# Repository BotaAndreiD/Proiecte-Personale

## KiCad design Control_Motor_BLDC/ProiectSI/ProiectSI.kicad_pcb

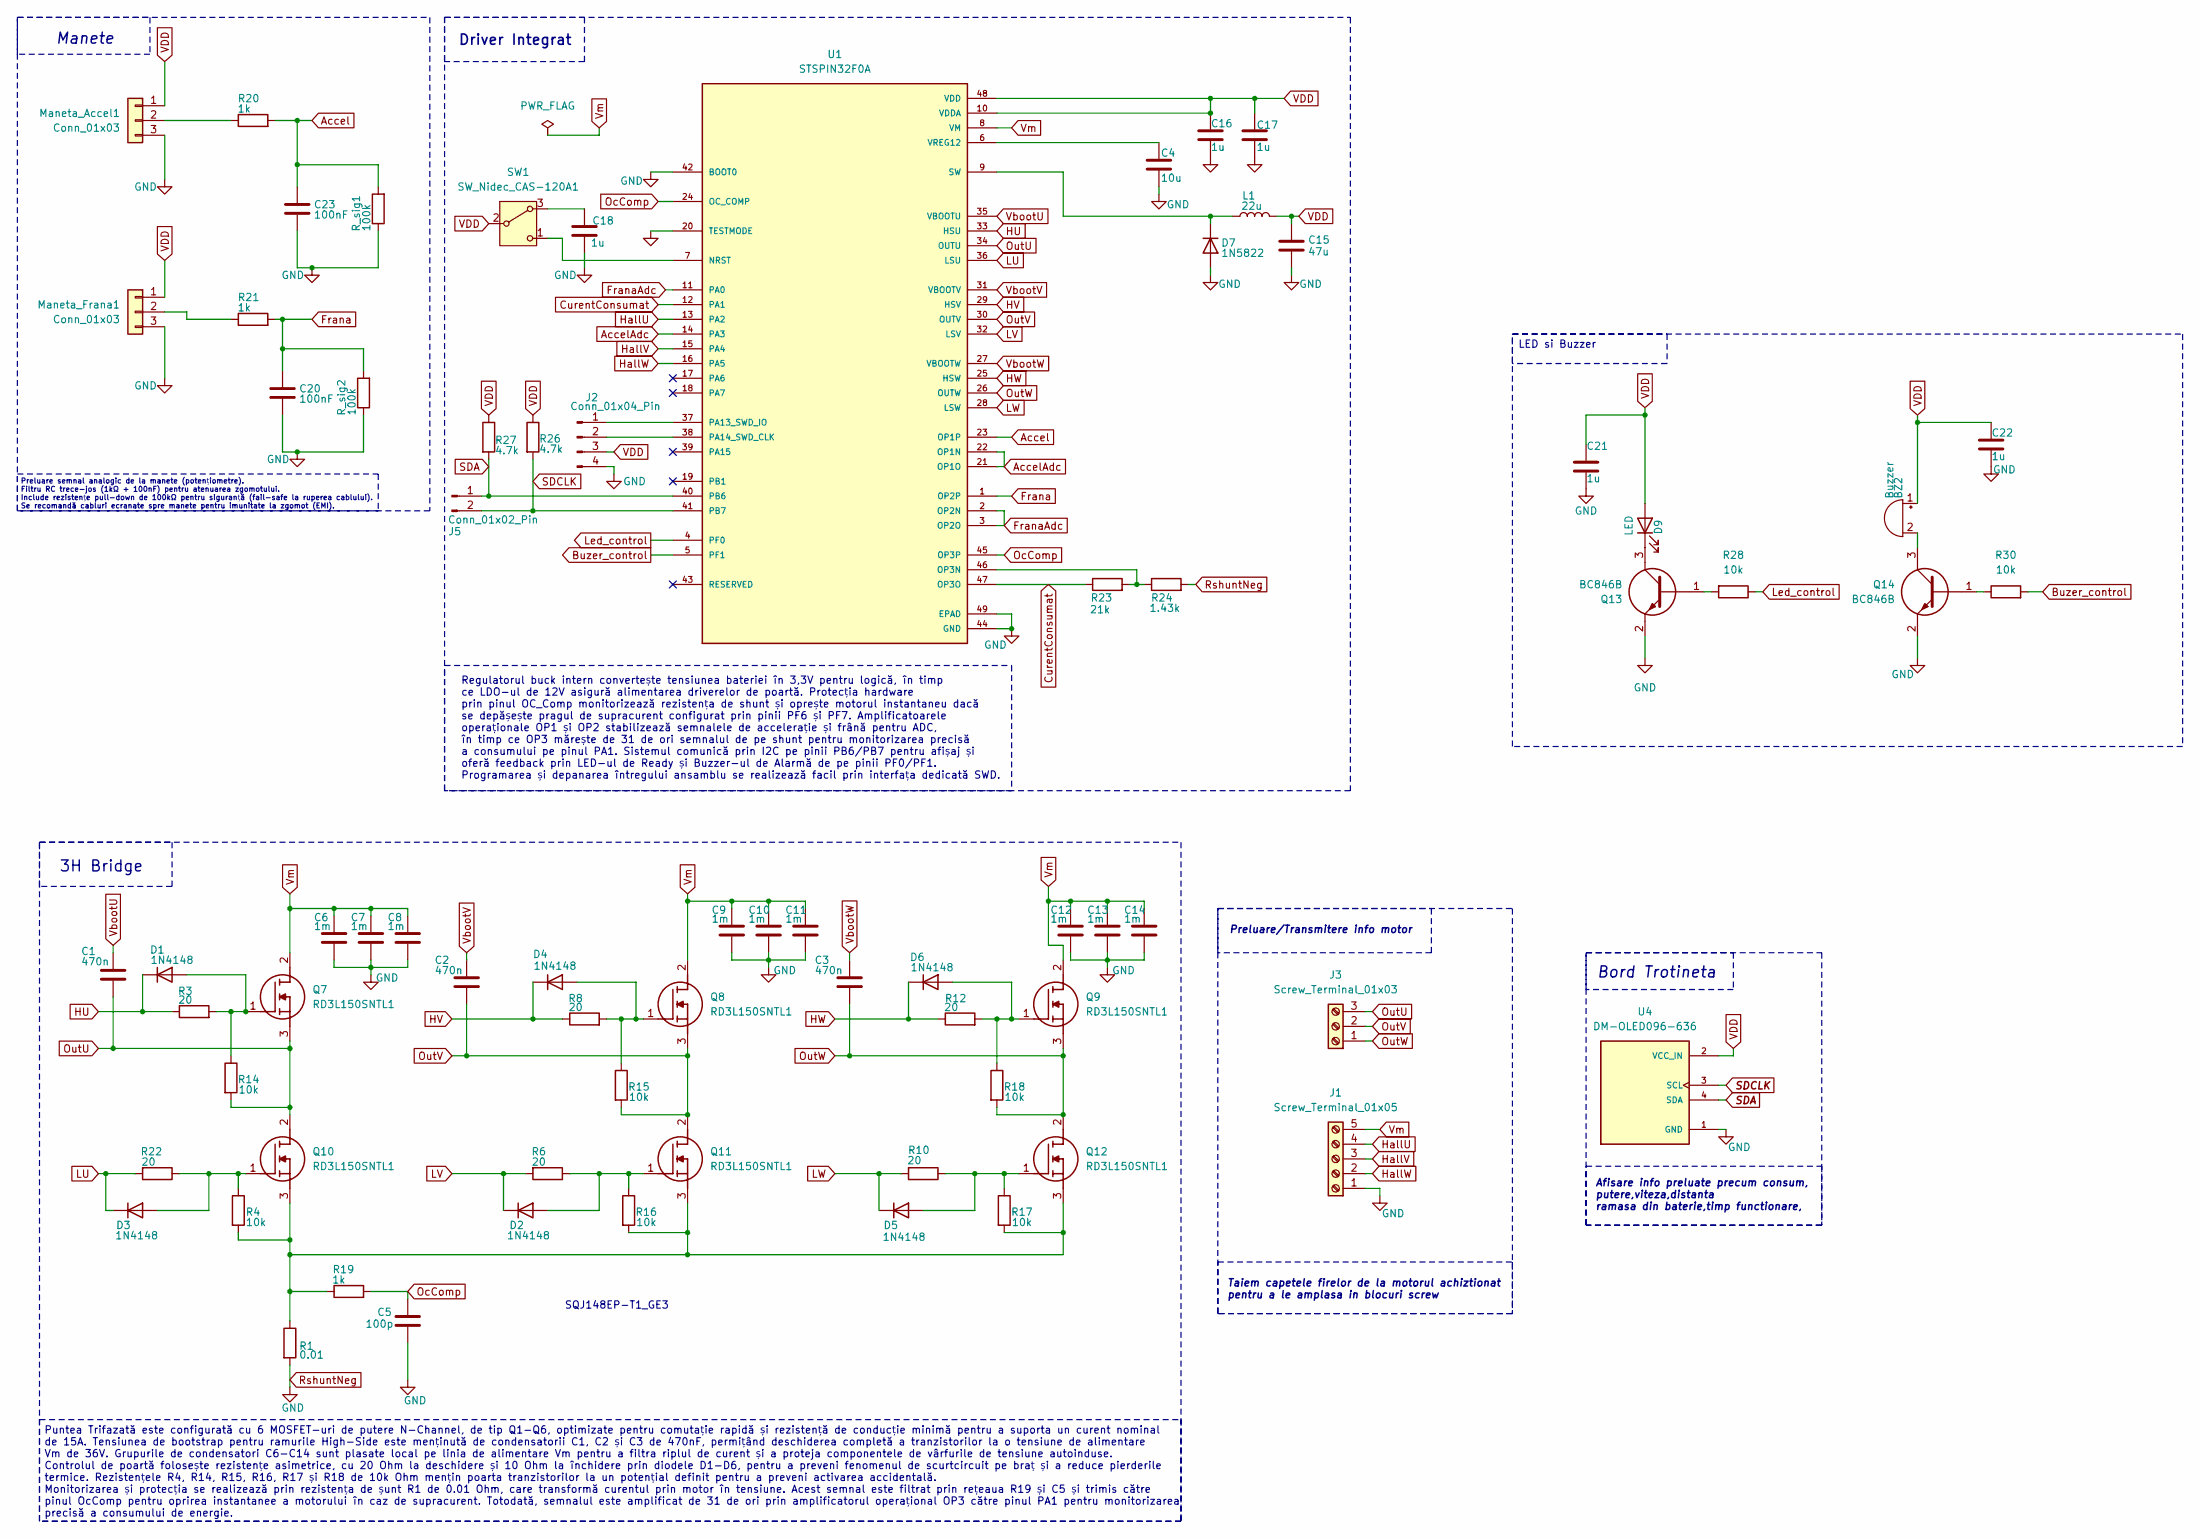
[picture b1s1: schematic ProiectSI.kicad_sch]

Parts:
BZ2: Buzzer; Buzzer_TDK_PS1240P02BT_D12.2mm_H6.5mm
C1, C2, C3: 470n; C_0603_1608Metric
C4: 10u; C_0603_1608Metric
C5: 100p; C_0603_1608Metric
C6, C7, C8, C9, C10, C11, C12, C13, C14: 1m; C_0603_1608Metric
C15: 47u; C_0603_1608Metric
C16, C17, C18, C21, C22: 1u; C_0603_1608Metric
C20, C23: 100nF; C_0603_1608Metric
D1, D2, D3, D4, D5, D6: 1N4148; D_0603_1608Metric
D7: 1N5822; D_0603_1608Metric
D9: LED; LED_0805_2012Metric
J1: Screw_Terminal_01x05; TerminalBlock_Phoenix_MPT-0,5-5-2.54_1x05_P2.54mm_Horizontal
J2: Conn_01x04_Pin; PinHeader_1x04_P1.00mm_Vertical
J3: Screw_Terminal_01x03; TerminalBlock_Phoenix_MKDS-1,5-3-5.08_1x03_P5.08mm_Horizont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
J5: Conn_01x02_Pin; PinHeader_1x02_P1.00mm_Vertical
L1: 22u; L_0603_1608Metric
Maneta_Accel1: Conn_01x03; PinHeader_1x03_P2.54mm_Vertical
Maneta_Frana1: Conn_01x03; PinHeader_1x03_P2.54mm_Vertical
Q7, Q8, Q9, Q10, Q11, Q12: RD3L150SNTL1; RD3P175SNFRATL; Manufacturer_Part_Number RD3L150SNTL1; Mouser Part Number 755-RD3L150SNTL1
Q13, Q14: BC846B; Manufacturer_Part_Number BC846B; Mouser Part Number 637-BC846B
R1: 0.01; R_0603_1608Metric
R3, R6, R8, R10, R12, R22: 20; R_0603_1608Metric
R4, R14, R15, R16, R17, R18, R28, R30: 10k; R_0603_1608Metric
R19, R20, R21: 1k; R_0603_1608Metric
R23: 21k; R_0603_1608Metric
R24: 1.43k; R_0603_1608Metric
R26, R27: 4.7k; R_0603_1608Metric
R_sig1, R_sig2: 100k; R_0603_1608Metric
SW1: SW_Nidec_CAS-120A1; Nidec_Copal_CAS-120A
U1: STSPIN32F0A; VQFN-48-1EP_7x7mm_P0.5mm_EP2.6x2.6mm_ThermalVias; PARTREV 2
U4: DM-OLED096-636; MODULE_DM-OLED096-636; PARTREV 2018-09-10

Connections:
Accel: C23.1, R20.2, R_sig1.2, U1.23 (OP1P); also elsewhere on the board
AccelAdc: U1.14 (PA3), U1.21 (OP1O), U1.22 (OP1N)
Buzer_control: R30.2, U1.5 (PF1)
CurentConsumat: R23.1, U1.12 (PA1), U1.47 (OP3O)
Frana: C20.1, R21.2, R_sig2.2, U1.1 (OP2P); also elsewhere on the board
FranaAdc: U1.2 (OP2N), U1.3 (OP2O), U1.11 (PA0)
HU: D1.1 (K), R3.1, U1.33 (HSU)
HV: D4.1 (K), R8.1, U1.29 (HSV)
HW: D6.1 (K), R12.1, U1.25 (HSW)
HallU: J1.4, U1.13 (PA2)
HallV: J1.3, U1.15 (PA4)
HallW: J1.2, U1.16 (PA5)
LU: D3.1 (K), R22.2, U1.36 (LSU)
LV: D2.1 (K), R6.2, U1.32 (LSV)
LW: D5.1 (K), R10.2, U1.28 (LSW)
Led_control: R28.1, U1.4 (PF0)
unnamed: BZ2.2 (-), Q14.3
unnamed 17: D1.2 (A), Q7.1 (G), R3.2, R14.1; also elsewhere on the board
unnamed 18: D2.2 (A), Q11.1 (G), R6.1, R16.1; also elsewhere on the board
unnamed 19: D3.2 (A), Q10.1 (G), R4.1, R22.1; also elsewhere on the board
unnamed 20: D4.2 (A), Q8.1 (G), R8.2, R15.1; also elsewhere on the board
unnamed 21: D5.2 (A), Q12.1 (G), R10.1, R17.1; also elsewhere on the board
unnamed 22: D6.2 (A), Q9.1 (G), R12.2, R18.1; also elsewhere on the board
unnamed: D7.1 (K), L1.1, U1.9 (SW)
unnamed: D9.1 (K), Q13.3
unnamed: J2.1, U1.37 (PA13_SWD_IO)
unnamed: J2.2, U1.38 (PA14_SWD_CLK)
unnamed: Q10.3 (S), Q11.3 (S), Q12.3 (S), R1.1, R4.2, R16.2, R17.2, R19.1
unnamed: Q13.1, R28.2
unnamed: Q14.1, R30.1
unnamed: C18.1, SW1.3 (A)
unnamed: SW1.1 (C), U1.7 (NRST)
unnamed: R23.2, R24.1, U1.46 (OP3N)
unnamed: C4.1, U1.6 (VREG12)
OcComp: C5.1, R19.2, U1.24 (OC_COMP), U1.45 (OP3P)
OutU: C1.2, J3.3, Q7.3 (S), Q10.2 (D), R14.2, U1.34 (OUTU)
OutV: C2.2, J3.2, Q8.3 (S), Q11.2 (D), R15.2, U1.30 (OUTV)
OutW: C3.2, J3.1, Q9.3 (S), Q12.2 (D), R18.2, U1.26 (OUTW)
RshuntNeg: C4.2, C5.2, C6.2, C7.2, C8.2, C9.2, C10.2, C11.2, C12.2, C13.2, C14.2, C15.2, C16.2, C17.2, C18.2, C20.2, C21.2, C22.2, C23.2, D7.2 (A), J1.1, J2.4, Maneta_Accel1.3, Maneta_Frana1.3, Q13.2, Q14.2, R1.2, R24.2, R_sig1.1, R_sig2.1, U1.20 (TESTMODE), U1.42 (BOOT0), U1.44 (GND), U1.49 (EPAD), U4.1 (GND); also elsewhere on the board
SDA: J5.1, R27.2, U1.40 (PB6), U4.4 (SDA)
SDCLK: J5.2, R26.2, U1.41 (PB7), U4.3 (SCL)
VDD: BZ2.1 (+), C15.1, C16.1, C17.1, C21.1, C22.1, D9.2 (A), J2.3, L1.2, Maneta_Accel1.1, Maneta_Frana1.1, R26.1, R27.1, SW1.2 (B), U1.10 (VDDA), U1.48 (VDD), U4.2 (VCC_IN); also elsewhere on the board
VbootU: C1.1, U1.35 (VBOOTU)
VbootV: C2.1, U1.31 (VBOOTV)
VbootW: C3.1, U1.27 (VBOOTW)
Vm: C6.1, C7.1, C8.1, C9.1, C10.1, C11.1, C12.1, C13.1, C14.1, J1.5, Q7.2 (D), Q8.2 (D), Q9.2 (D), U1.8 (VM)

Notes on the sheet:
Preluare semnal analogic de la manete (potențiometre). Filtru RC trece-jos (1kΩ + 100nF) pentru atenuarea zgomotului. Include rezistențe pull-down de 100kΩ pentru siguranță (fail-safe la ruperea cablului). Se recomandă cabluri ecranate spre manete pentru imunitate la zgomot (EMI).
SQJ148EP-T1_GE3
Manete
Preluare/Transmitere info motor
Puntea Trifazată este configurată cu 6 MOSFET-uri de putere N-Channel, de tip Q1-Q6, optimizate pentru comutație rapidă și rezistență de conducție minimă pentru a suporta un curent nominal de 15A. Tensiunea de bootstrap pentru ramurile High-Side este menținută de condensatorii C1, C2 și C3 de 470nF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
Driver Integrat
Afisare info preluate precum consum, putere,viteza,distanta ramasa din baterie,timp functionare,
Regulatorul buck intern convertește tensiunea bateriei în 3,3V pentru logică, în timp ce LDO-ul de 12V asigură alimentarea driverelor de poartă. Protecția hardware prin pinul OC_Comp monitorizează rezistența de shunt și oprește motorul instantaneu dacă se depășește pragul de supracurent configurat 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
Bord Trotineta
3H Bridge
Taiem capetele firelor de la motorul achiztionat pentru a le amplasa in blocuri screw
LED si Buzzer

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
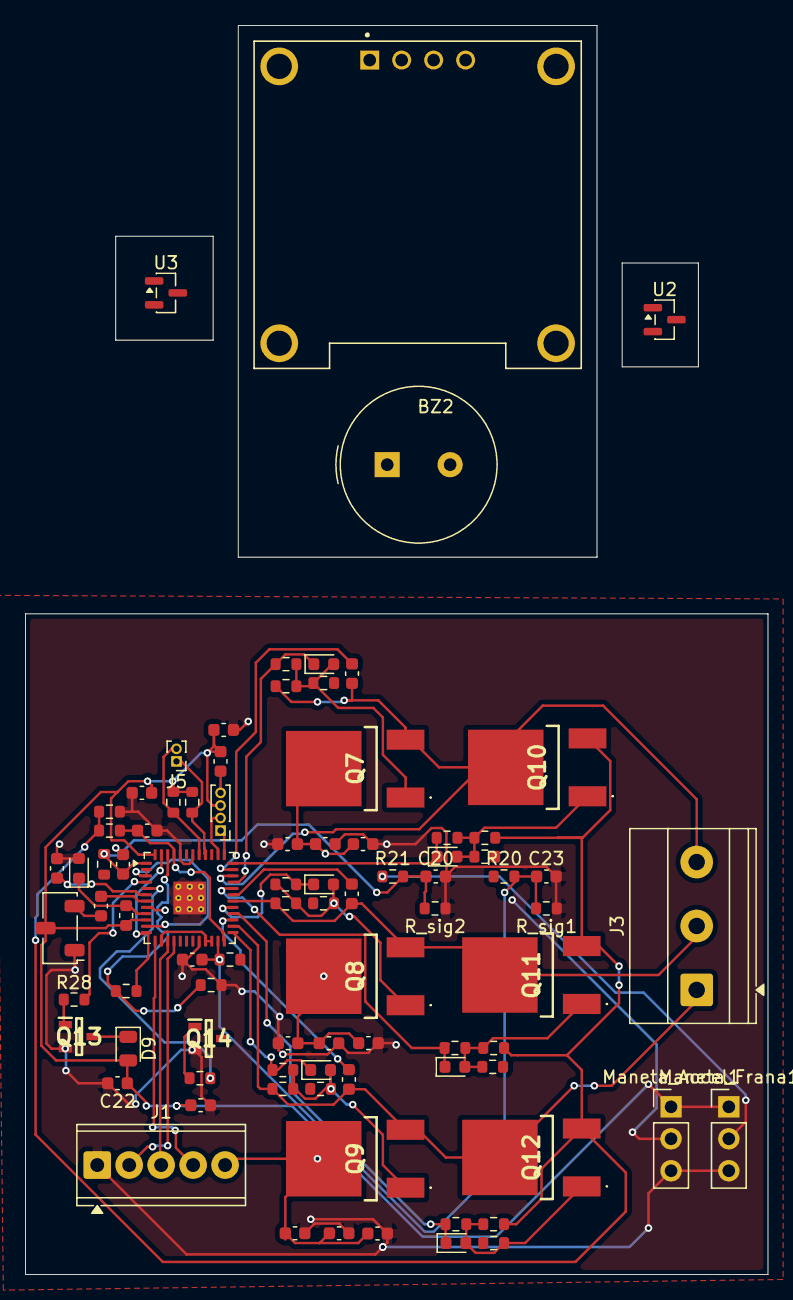
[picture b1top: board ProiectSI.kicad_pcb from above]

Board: 4 copper layers, 59.0 x 99.2 mm, 85 parts (0 on the bottom side), 50 nets.

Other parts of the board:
C19, C20#2: 7.96n; C_0603_1608Metric
R2, R5, R7, R9, R11, R13: 10; R_0603_1608Metric
R20#2, R21#2: 1k; R_0603_1608Metric
U2, U3: DRV5055A2xDBZxQ1; SOT-23

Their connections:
Accel: C19.1, R20#2.2; also elsewhere on the board
Frana: C20#2.1, R21#2.2; also elsewhere on the board
unnamed 17: R2.1; also elsewhere on the board
unnamed 18: R7.2; also elsewhere on the board
unnamed 19: R5.2; also elsewhere on the board
unnamed 20: R9.1; also elsewhere on the board
unnamed 21: R11.2; also elsewhere on the board
unnamed 22: R13.1; also elsewhere on the board
RshuntNeg: C19.2, C20#2.2, U2.3 (GND), U3.3 (GND); also elsewhere on the board
VDD: U2.1 (VCC), U3.1 (VCC); also elsewhere on the board

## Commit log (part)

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2025-09-25 Moved files in another file for better organization
2025-09-25 Adăugat proiectul Simulare NE555 în Proiecte-Personale
2025-09-25 Șters folderul DigitalWrite corupt
2025-11-06 Reorganize repo
2025-11-06 Integrare: Proiectele Vivado si ORCAD adaugate in proiectul principal.
2026-02-17 Adăugat Proiect IV: Fișier LabVIEW și documentație PDF
2026-02-17 Redenumit folderul ProiectIV în PID-implementat-in-LabVIEW pentru claritate
2026-02-17 Adăugat ProiectareSursaAlimentareLTspice fără fișiere mari
2026-02-17 Eliminat folderul duplicat ProiectSurse, păstrat doar ProiectareSursaAlimentareLTspice
2026-03-14 Add Proiectare_Interfata_Analogica
2026-03-14 Fix Proiectare_Interfata_Analogica as regular folder
2026-04-29 Adaugat proiect SI
2026-04-29 Realizat layout PCB
2026-04-30 Adaugat text informativ in schematic pentru puntea 3H
2026-04-30 Adaugat clarificare schematic la punte
2026-05-01 Adaugat 2 proiecte
2026-05-05 Adaugat cod pentru optimizarea functie de Marcare_LSB
2026-05-13 Adaugat implementare tranzistori la filtru TowThomas1
2026-05-16 Modificare proiecte
2026-05-19 Adaugat fisiere proiect ThowThomas
2026-05-23 Modificari proiect
2026-05-27 Add PGA simulation files using Git LFS
2026-05-28 Finalizare proiect
2026-06-08 Adaugat deecodare
